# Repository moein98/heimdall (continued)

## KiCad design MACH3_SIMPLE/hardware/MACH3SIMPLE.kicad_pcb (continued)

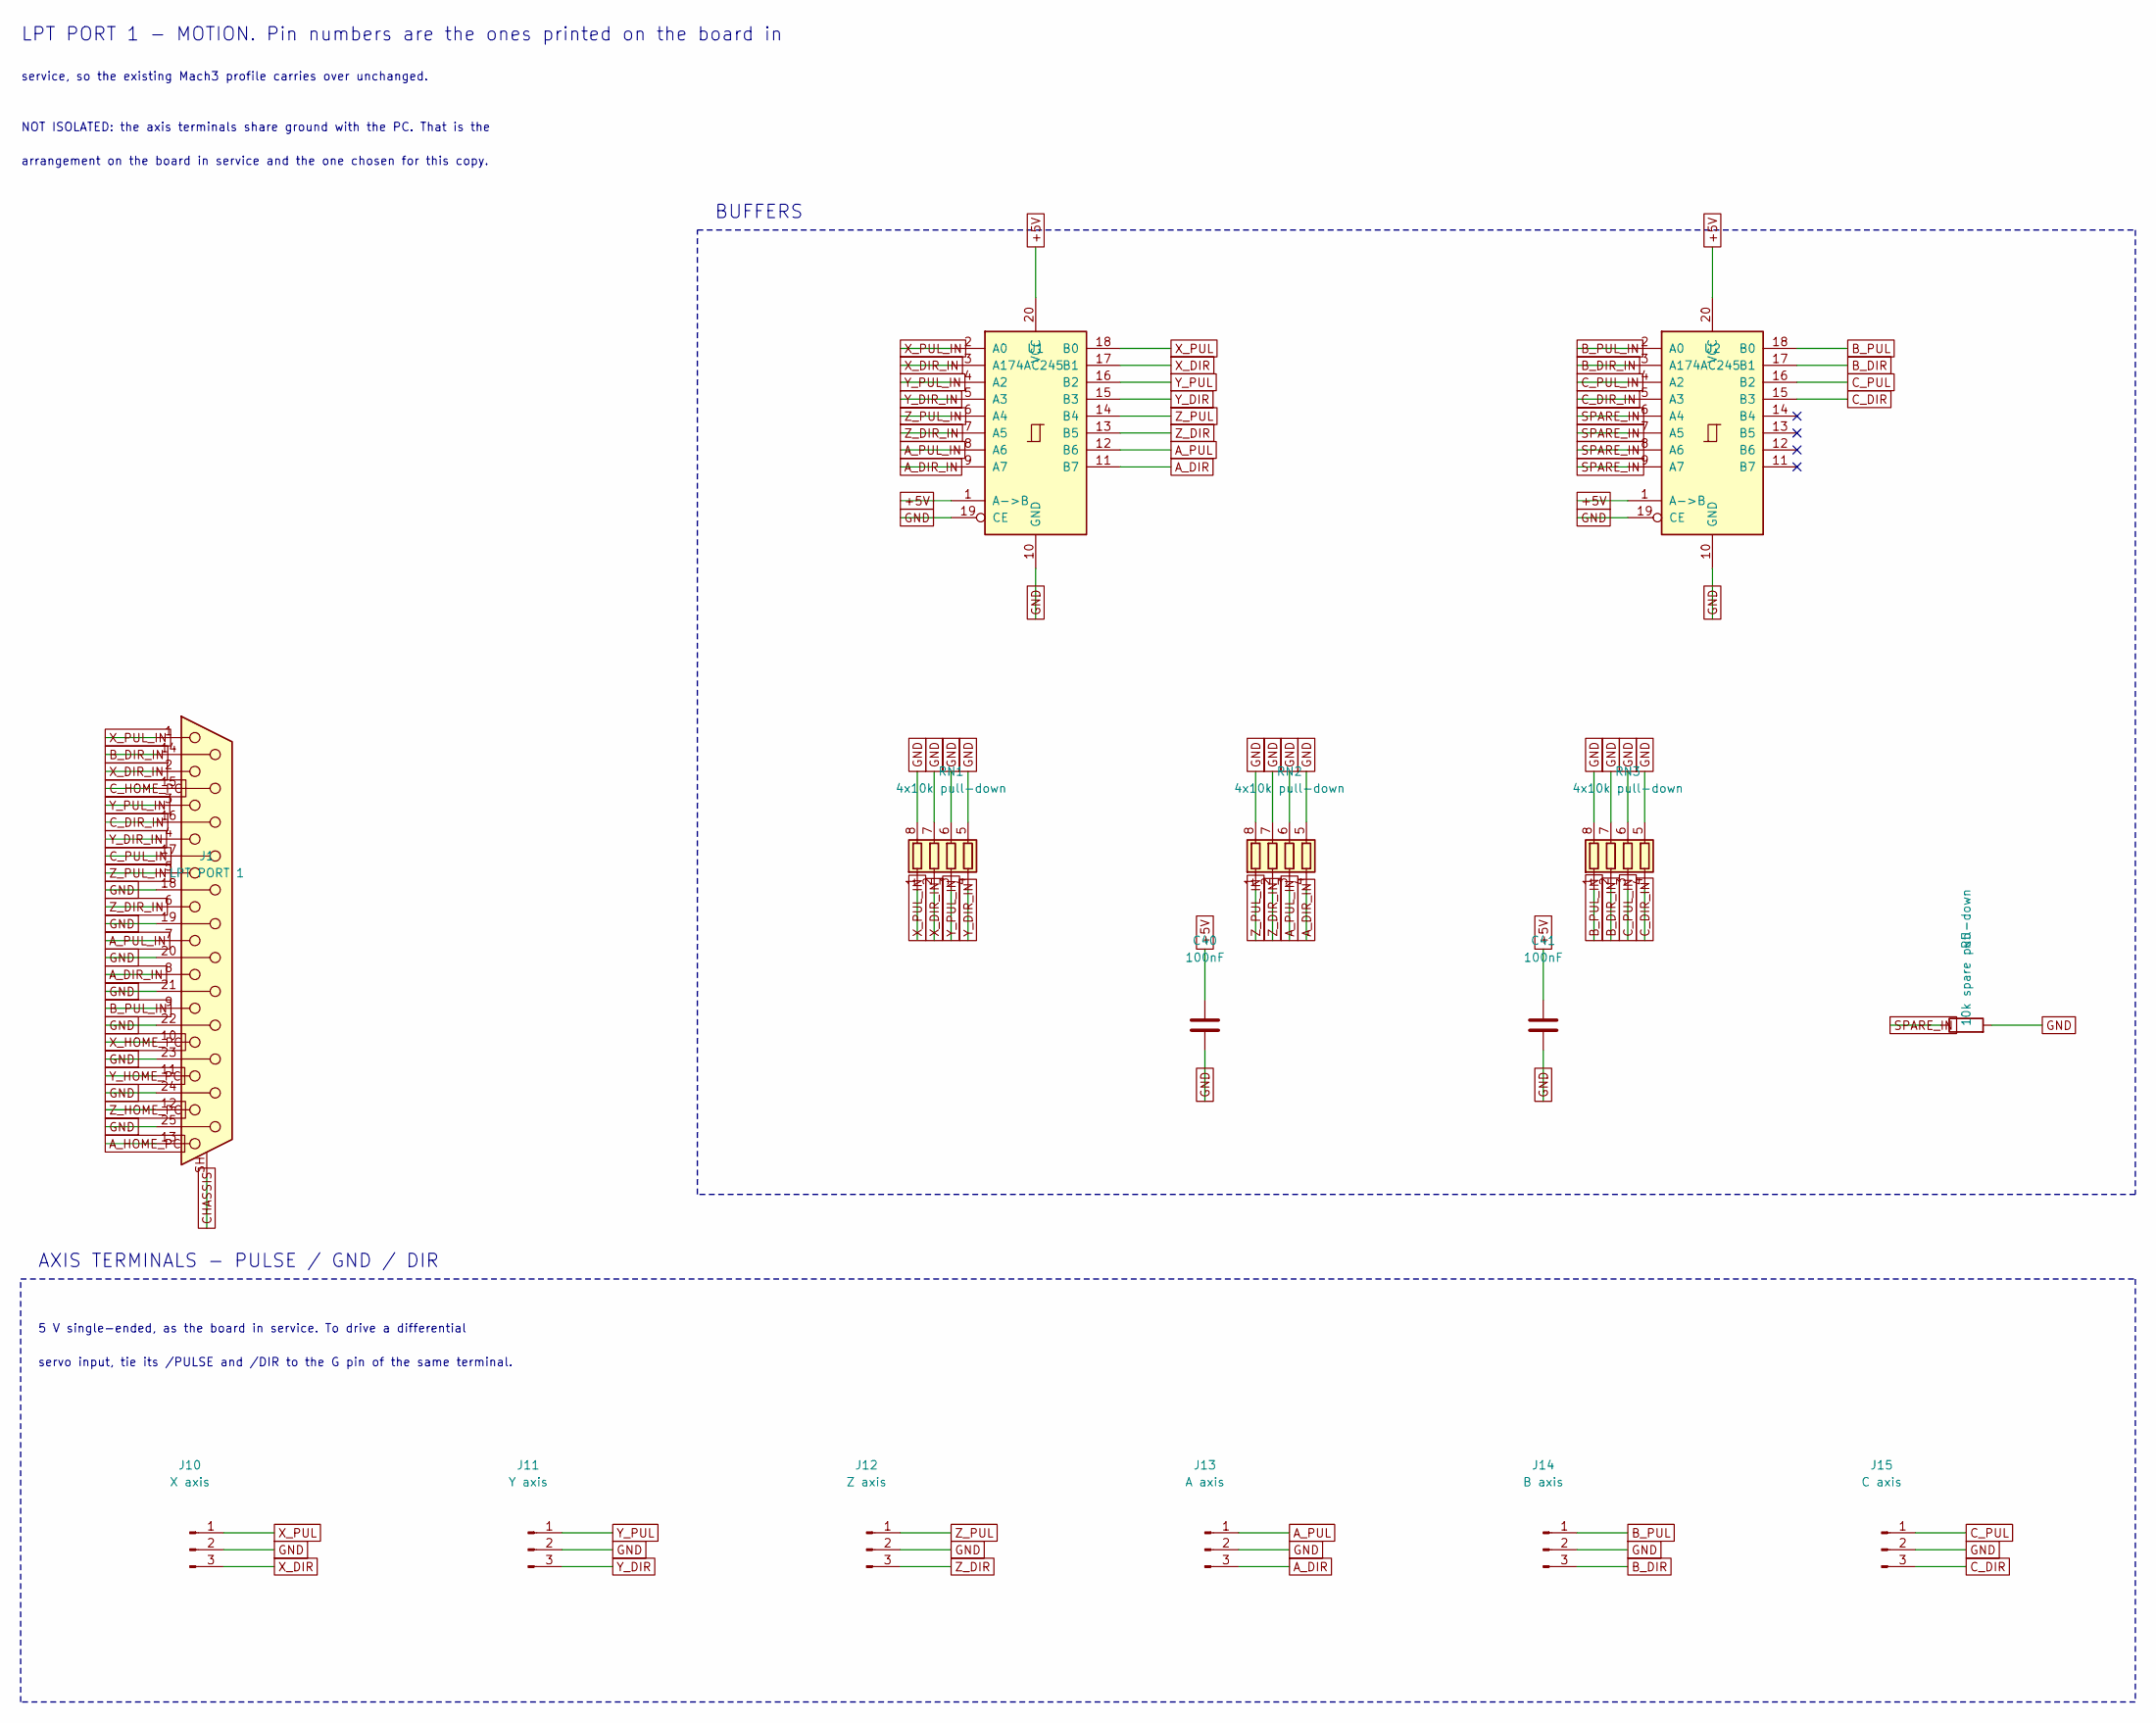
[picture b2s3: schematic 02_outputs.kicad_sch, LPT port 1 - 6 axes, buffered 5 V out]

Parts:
C40, C41: 100nF; C_0603_1608Metric
J1: LPT PORT 1; DSUB-25_Socket_Horizontal_P2.77x2.84mm_EdgePinOffset7.70mm_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
J10: X axis; TerminalBlock_Phoenix_MKDS-1,5-3_1x03_P5.00mm_Horizontal
J11: Y axis; TerminalBlock_Phoenix_MKDS-1,5-3_1x03_P5.00mm_Horizontal
J12: Z axis; TerminalBlock_Phoenix_MKDS-1,5-3_1x03_P5.00mm_Horizontal
J13: A axis; TerminalBlock_Phoenix_MKDS-1,5-3_1x03_P5.00mm_Horizontal
J14: B axis; TerminalBlock_Phoenix_MKDS-1,5-3_1x03_P5.00mm_Horizontal
J15: C axis; TerminalBlock_Phoenix_MKDS-1,5-3_1x03_P5.00mm_Horizontal
R5: 10k spare pull-down; R_0603_1608Metric
RN1, RN2, RN3: 4x10k pull-down; R_Array_Convex_4x0603
U1, U2: 74AC245; SOIC-20W_7.5x12.8mm_P1.27mm

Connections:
+5V: C40.1, C41.1, U1.1 (A->B), U1.20 (VCC), U2.1 (A->B), U2.20 (VCC); also elsewhere on the board
A_DIR: J13.3, U1.11 (B7)
A_DIR_IN: J1.8, RN2.4 (R4.1), U1.9 (A7)
A_HOME_PC: J1.13; also elsewhere on the board
A_PUL: J13.1, U1.12 (B6)
A_PUL_IN: J1.7, RN2.3 (R3.1), U1.8 (A6)
B_DIR: J14.3, U2.17 (B1)
B_DIR_IN: J1.14, RN3.2 (R2.1), U2.3 (A1)
B_PUL: J14.1, U2.18 (B0)
B_PUL_IN: J1.9, RN3.1 (R1.1), U2.2 (A0)
CHASSIS: J1.SH (PAD); also elsewhere on the board
C_DIR: J15.3, U2.15 (B3)
C_DIR_IN: J1.16, RN3.4 (R4.1), U2.5 (A3)
C_HOME_PC: J1.15; also elsewhere on the board
C_PUL: J15.1, U2.16 (B2)
C_PUL_IN: J1.17, RN3.3 (R3.1), U2.4 (A2)
GND: C40.2, C41.2, J1.18, J1.19, J1.20, J1.21, J1.22, J1.23, J1.24, J1.25, J10.2, J11.2, J12.2, J13.2, J14.2, J15.2, R5.2, RN1.5 (R4.2), RN1.6 (R3.2), RN1.7 (R2.2), RN1.8 (R1.2), RN2.5 (R4.2), RN2.6 (R3.2), RN2.7 (R2.2), RN2.8 (R1.2), RN3.5 (R4.2), RN3.6 (R3.2), RN3.7 (R2.2), RN3.8 (R1.2), U1.10 (GND), U1.19 (CE), U2.10 (GND), U2.19 (CE); also elsewhere on the board
SPARE_IN: R5.1, U2.6 (A4), U2.7 (A5), U2.8 (A6), U2.9 (A7)
X_DIR: J10.3, U1.17 (B1)
X_DIR_IN: J1.2, RN1.2 (R2.1), U1.3 (A1)
X_HOME_PC: J1.10; also elsewhere on the board
X_PUL: J10.1, U1.18 (B0)
X_PUL_IN: J1.1, RN1.1 (R1.1), U1.2 (A0)
Y_DIR: J11.3, U1.15 (B3)
Y_DIR_IN: J1.4, RN1.4 (R4.1), U1.5 (A3)
Y_HOME_PC: J1.11; also elsewhere on the board
Y_PUL: J11.1, U1.16 (B2)
Y_PUL_IN: J1.3, RN1.3 (R3.1), U1.4 (A2)
Z_DIR: J12.3, U1.13 (B5)
Z_DIR_IN: J1.6, RN2.2 (R2.1), U1.7 (A5)
Z_HOME_PC: J1.12; also elsewhere on the board
Z_PUL: J12.1, U1.14 (B4)
Z_PUL_IN: J1.5, RN2.1 (R1.1), U1.6 (A4)

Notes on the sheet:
LPT PORT 1 - MOTION. Pin numbers are the ones printed on the board in
service, so the existing Mach3 profile carries over unchanged.
NOT ISOLATED: the axis terminals share ground with the PC. That is the
arrangement on the board in service and the one chosen for this copy.
BUFFERS
AXIS TERMINALS - PULSE / GND / DIR
5 V single-ended, as the board in service. To drive a differential
servo input, tie its /PULSE and /DIR to the G pin of the same terminal.

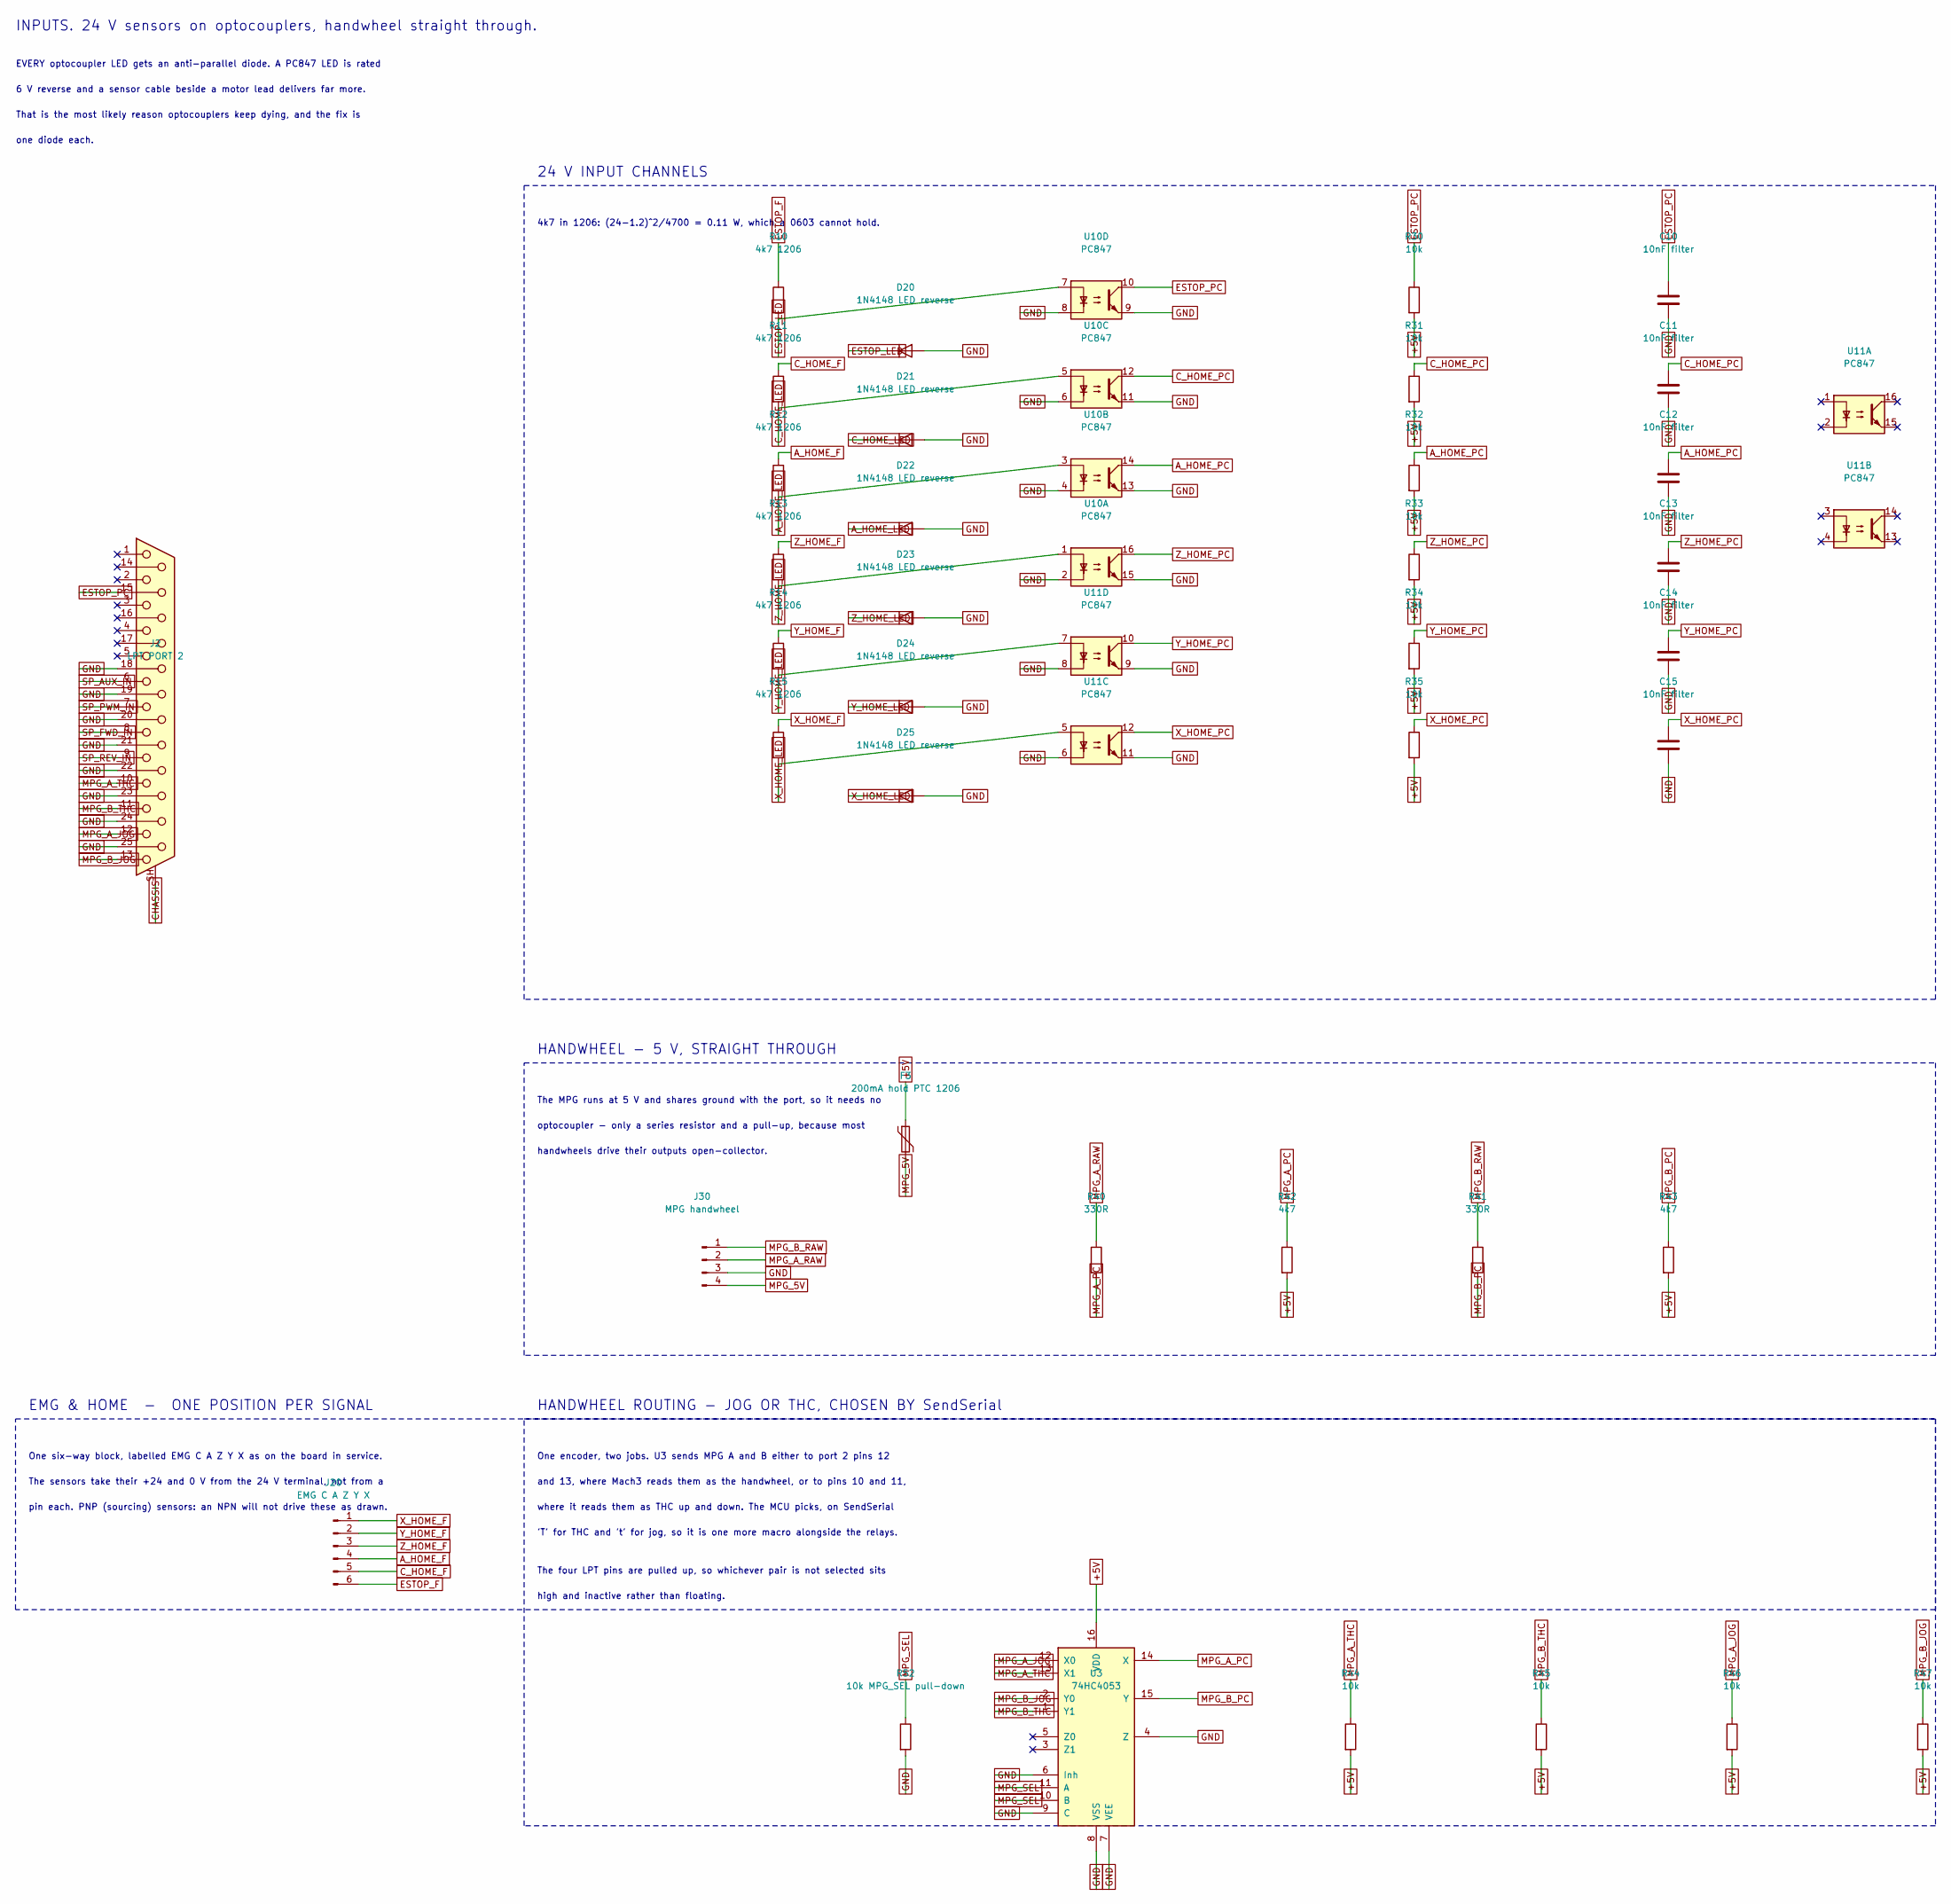
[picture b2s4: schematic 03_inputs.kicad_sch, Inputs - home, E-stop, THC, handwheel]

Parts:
C10, C11, C12, C13, C14, C15: 10nF filter; C_0603_1608Metric
D20, D21, D22, D23, D24, D25: 1N4148 LED reverse; D_SOD-123
F3: 200mA hold PTC 1206; Fuse_1206_3216Metric
J2: LPT PORT 2; DSUB-25_Socket_Horizontal_P2.77x2.84mm_EdgePinOffset7.70mm_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
J20: EMG C A Z Y X; TerminalBlock_Phoenix_MKDS-1,5-6_1x06_P5.00mm_Horizontal
J30: MPG handwheel; TerminalBlock_Phoenix_MKDS-1,5-4_1x04_P5.00mm_Horizontal
R10, R11, R12, R13, R14, R15: 4k7 1206; R_1206_3216Metric
R30, R31, R32, R33, R34, R35, R44, R45, R46, R47: 10k; R_0603_1608Metric
R40, R41: 330R; R_0603_1608Metric
R42, R43: 4k7; R_0603_1608Metric
R52: 10k MPG_SEL pull-down; R_0603_1608Metric
U3: 74HC4053; SOIC-16_3.9x9.9mm_P1.27mm
U10, U11: PC847; SMDIP-16_W9.53mm

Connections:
+5V: F3.1, R30.2, R31.2, R32.2, R33.2, R34.2, R35.2, R42.2, R43.2, R44.2, R45.2, R46.2, R47.2, U3.16 (VDD); also elsewhere on the board
A_HOME_F: J20.4, R12.1
A_HOME_LED: D22.1 (K), R12.2, U10.3
A_HOME_PC: C12.1, R32.1, U10.14; also elsewhere on the board
CHASSIS: J2.SH (PAD); also elsewhere on the board
C_HOME_F: J20.5, R11.1
C_HOME_LED: D21.1 (K), R11.2, U10.5
C_HOME_PC: C11.1, R31.1, U10.12; also elsewhere on the board
ESTOP_F: J20.6, R10.1
ESTOP_LED: D20.1 (K), R10.2, U10.7
ESTOP_PC: C10.1, J2.15, R30.1, U10.10
GND: C10.2, C11.2, C12.2, C13.2, C14.2, C15.2, D20.2 (A), D21.2 (A), D22.2 (A), D23.2 (A), D24.2 (A), D25.2 (A), J2.18, J2.19, J2.20, J2.21, J2.22, J2.23, J2.24, J2.25, J30.3, R52.2, U3.4 (Z), U3.6 (Inh), U3.7 (VEE), U3.8 (VSS), U3.9 (C), U10.2, U10.4, U10.6, U10.8, U10.9, U10.11, U10.13, U10.15, U11.6, U11.8, U11.9, U11.11; also elsewhere on the board
MPG_5V: F3.2, J30.4
MPG_A_JOG: J2.12, R46.1, U3.12 (X0)
MPG_A_PC: R40.2, R42.1, U3.14 (X)
MPG_A_RAW: J30.2, R40.1
MPG_A_THC: J2.10, R44.1, U3.13 (X1)
MPG_B_JOG: J2.13, R47.1, U3.2 (Y0)
MPG_B_PC: R41.2, R43.1, U3.15 (Y)
MPG_B_RAW: J30.1, R41.1
MPG_B_THC: J2.11, R45.1, U3.1 (Y1)
MPG_SEL: R52.1, U3.10 (B), U3.11 (A); also elsewhere on the board
SP_AUX_IN: J2.6; also elsewhere on the board
SP_FWD_IN: J2.8; also elsewhere on the board
SP_PWM_IN: J2.7; also elsewhere on the board
SP_REV_IN: J2.9; also elsewhere on the board
X_HOME_F: J20.1, R15.1
X_HOME_LED: D25.1 (K), R15.2, U11.5
X_HOME_PC: C15.1, R35.1, U11.12; also elsewhere on the board
Y_HOME_F: J20.2, R14.1
Y_HOME_LED: D24.1 (K), R14.2, U11.7
Y_HOME_PC: C14.1, R34.1, U11.10; also elsewhere on the board
Z_HOME_F: J20.3, R13.1
Z_HOME_LED: D23.1 (K), R13.2, U10.1
Z_HOME_PC: C13.1, R33.1, U10.16; also elsewhere on the board

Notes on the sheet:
INPUTS. 24 V sensors on optocouplers, handwheel straight through.
EVERY optocoupler LED gets an anti-parallel diode. A PC847 LED is rated
6 V reverse and a sensor cable beside a motor lead delivers far more.
That is the most likely reason optocouplers keep dying, and the fix is
one diode each.
24 V INPUT CHANNELS
4k7 in 1206: (24-1.2)^2/4700 = 0.11 W, which a 0603 cannot hold.
HANDWHEEL - 5 V, STRAIGHT THROUGH
The MPG runs at 5 V and shares ground with the port, so it needs no
optocoupler - only a series resistor and a pull-up, because most
handwheels drive their outputs open-collector.
HANDWHEEL ROUTING - JOG OR THC, CHOSEN BY SendSerial
One encoder, two jobs. U3 sends MPG A and B either to port 2 pins 12
and 13, where Mach3 reads them as the handwheel, or to pins 10 and 11,
where it reads them as THC up and down. The MCU picks, on SendSerial
'T' for THC and 't' for jog, so it is one more macro alongside the relays.
The four LPT pins are pulled up, so whichever pair is not selected sits
high and inactive rather than floating.
EMG & HOME - ONE POSITION PER SIGNAL
One six-way block, labelled EMG C A Z Y X as on the board in service.
The sensors take their +24 and 0 V from the 24 V terminal, not from a
pin each. PNP (sourcing) sensors: an NPN will not drive these as drawn.

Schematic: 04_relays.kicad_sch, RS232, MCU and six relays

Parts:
C20, C21, C22, C23, C30, C31, C32, C42: 100nF; C_0603_1608Metric
C33, C34: 22pF; C_0603_1608Metric
C35: 10nF; C_0603_1608Metric
D30: SERIAL; LED_0603_1608Metric
D40, D41, D42, D43, D44, D45: 1N4148 flyback; D_SOD-123
D50: KA; LED_0603_1608Metric
D51: KB; LED_0603_1608Metric
D52: KC; LED_0603_1608Metric
D53: KD; LED_0603_1608Metric
D54: KE; LED_0603_1608Metric
D55: KF; LED_0603_1608Metric
J40: Relay A; TerminalBlock_Phoenix_MKDS-1,5-3_1x03_P5.00mm_Horizontal
J41: Relay B; TerminalBlock_Phoenix_MKDS-1,5-3_1x03_P5.00mm_Horizontal
J42: Relay C; TerminalBlock_Phoenix_MKDS-1,5-3_1x03_P5.00mm_Horizontal
J43: Relay D; TerminalBlock_Phoenix_MKDS-1,5-3_1x03_P5.00mm_Horizontal
J44: Relay E; TerminalBlock_Phoenix_MKDS-1,5-3_1x03_P5.00mm_Horizontal
J45: Relay F; TerminalBlock_Phoenix_MKDS-1,5-3_1x03_P5.00mm_Horizontal
J50: RS232 RX TX GND; TerminalBlock_Phoenix_MKDS-1,5-3_1x03_P5.00mm_Horizontal
J60: ICSP; IDC-Header_2x05_P2.54mm_Vertical
K1, K2, K3, K4, K5, K6: JQC-3FF-024-1Z; Relay_SPDT_Hongfa_JQC-3FF_0XX-1Z
Q1, Q2, Q3, Q4, Q5, Q6: 2N7002; SOT-23
R50, R70, R71, R72, R73, R74, R75, R80, R81, R82, R83, R84, R85: 10k; R_0603_1608Metric
R51, R60, R61, R62, R63, R64, R65: 1k; R_0603_1608Metric
U20: MAX3232; SOIC-16_3.9x9.9mm_P1.27mm
U21: ATmega328P-AU; TQFP-32_7x7mm_P0.8mm
Y1: 16MHz; Crystal_SMD_3225-4Pin_3.2x2.5mm

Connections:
+5V: C22.2, C30.1, C31.1, C32.1, C42.1, J60.2 (VCC), R50.2, U20.16 (VCC), U21.4 (VCC), U21.6 (VCC), U21.18 (AVCC); also elsewhere on the board
C1N: C20.2, U20.3 (C1-)
C1P: C20.1, U20.1 (C1+)
C2N: C21.2, U20.5 (C2-)
C2P: C21.1, U20.4 (C2+)
GND: C23.2, C30.2, C31.2, C32.2, C33.2, C34.2, C35.2, C42.2, D30.1 (K), J50.3, J60.4 (GND), J60.6 (GND), J60.8 (GND), J60.10 (GND), Q1.2 (S), Q2.2 (S), Q3.2 (S), Q4.2 (S), Q5.2 (S), Q6.2 (S), R70.2, R71.2, R72.2, R73.2, R74.2, R75.2, U20.8 (R2IN), U20.10 (T2IN), U20.15 (GND), U21.3 (GND), U21.5 (GND), U21.19 (ADC6), U21.21 (GND), U21.22 (ADC7), Y1.2 (G), Y1.4 (G); also elsewhere on the board
ICSP_MISO: J60.9 (MISO), U21.16 (PB4)
ICSP_MOSI: J60.1 (MOSI), U21.15 (PB3)
ICSP_SCK: J60.7 (SCK), U21.17 (PB5)
KA_COM: J40.2, K1.11
KA_NC: J40.3, K1.12
KA_NO: J40.1, K1.14
KB_COM: J41.2, K2.11
KB_NC: J41.3, K2.12
KB_NO: J41.1, K2.14
KC_COM: J42.2, K3.11
KC_NC: J42.3, K3.12
KC_NO: J42.1, K3.14
KD_COM: J43.2, K4.11
KD_NC: J43.3, K4.12
KD_NO: J43.1, K4.14
KE_COM: J44.2, K5.11
KE_NC: J44.3, K5.12
KE_NO: J44.1, K5.14
KF_COM: J45.2, K6.11
KF_NC: J45.3, K6.12
KF_NO: J45.1, K6.14
MCU_LED: R51.1, U21.14 (PB2)
MCU_RESET: C35.1, J60.5 (~RST), R50.1, U21.29 (~RESET/PC6)
MCU_RX: U20.12 (R1OUT), U21.30 (PD0)
MCU_TX: U20.11 (T1IN), U21.31 (PD1)
MPG_SEL: U21.13 (PB1); also elsewhere on the board
unnamed: D30.2 (A), R51.2
unnamed: D50.2 (A), R80.2
unnamed: D51.2 (A), R81.2
unnamed: D52.2 (A), R82.2
unnamed: D53.2 (A), R83.2
unnamed: D54.2 (A), R84.2
unnamed: D55.2 (A), R85.2
unnamed: Q1.1 (G), R60.2
unnamed: Q2.1 (G), R61.2
unnamed: Q3.1 (G), R62.2
unnamed: Q4.1 (G), R63.2
unnamed: Q5.1 (G), R64.2
unnamed: Q6.1 (G), R65.2
RELC_A: D40.2 (A), D50.1 (K), K1.A2, Q1.3 (D)
RELC_B: D41.2 (A), D51.1 (K), K2.A2, Q2.3 (D)
RELC_C: D42.2 (A), D52.1 (K), K3.A2, Q3.3 (D)
RELC_D: D43.2 (A), D53.1 (K), K4.A2, Q4.3 (D)
RELC_E: D44.2 (A), D54.1 (K), K5.A2, Q5.3 (D)
RELC_F: D45.2 (A), D55.1 (K), K6.A2, Q6.3 (D)
REL_A: R60.1, R70.1, U21.1 (PD3)
REL_B: R61.1, R71.1, U21.2 (PD4)
REL_C: R62.1, R72.1, U21.9 (PD5)
REL_D: R63.1, R73.1, U21.10 (PD6)
REL_E: R64.1, R74.1, U21.11 (PD7)
REL_F: R65.1, R75.1, U21.12 (PB0)
RS232_RX: J50.1, U20.13 (R1IN)
RS232_TX: J50.2, U20.14 (T1OUT)
V24: D40.1 (K), D41.1 (K), D42.1 (K), D43.1 (K), D44.1 (K), D45.1 (K), K1.A1, K2.A1, K3.A1, K4.A1, K5.A1, K6.A1, R80.1, R81.1, R82.1, R83.1, R84.1, R85.1; also elsewhere on the board
VSN: C23.1, U20.6 (VS-)
VSP: C22.1, U20.2 (VS+)
XTAL1: C33.1, U21.7 (XTAL1/PB6), Y1.3
XTAL2: C34.1, U21.8 (XTAL2/PB7), Y1.1

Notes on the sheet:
RS232 RELAY BANK. SendSerial("A").."F" on, "a".."f" off - the same
protocol as the board in service, so existing macros keep working.
RS232 AND MCU
The ATmega arrives blank: program it through J60 with a USBasp
(firmware/build.sh flash), which also sets the fuses for the 16 MHz
crystal Y1: low FF, high D9, extended FD. The factory fuses select the
internal RC, which is trimmed only to 10 percent. Serial is 9600 8N1.
SIX RELAYS - 24 V COILS ONLY
The contacts switch 24 V Finder coils. Nothing on this board touches
mains. A Finder coil is 20-60 mA, so a 10 A contact is heavily derated.

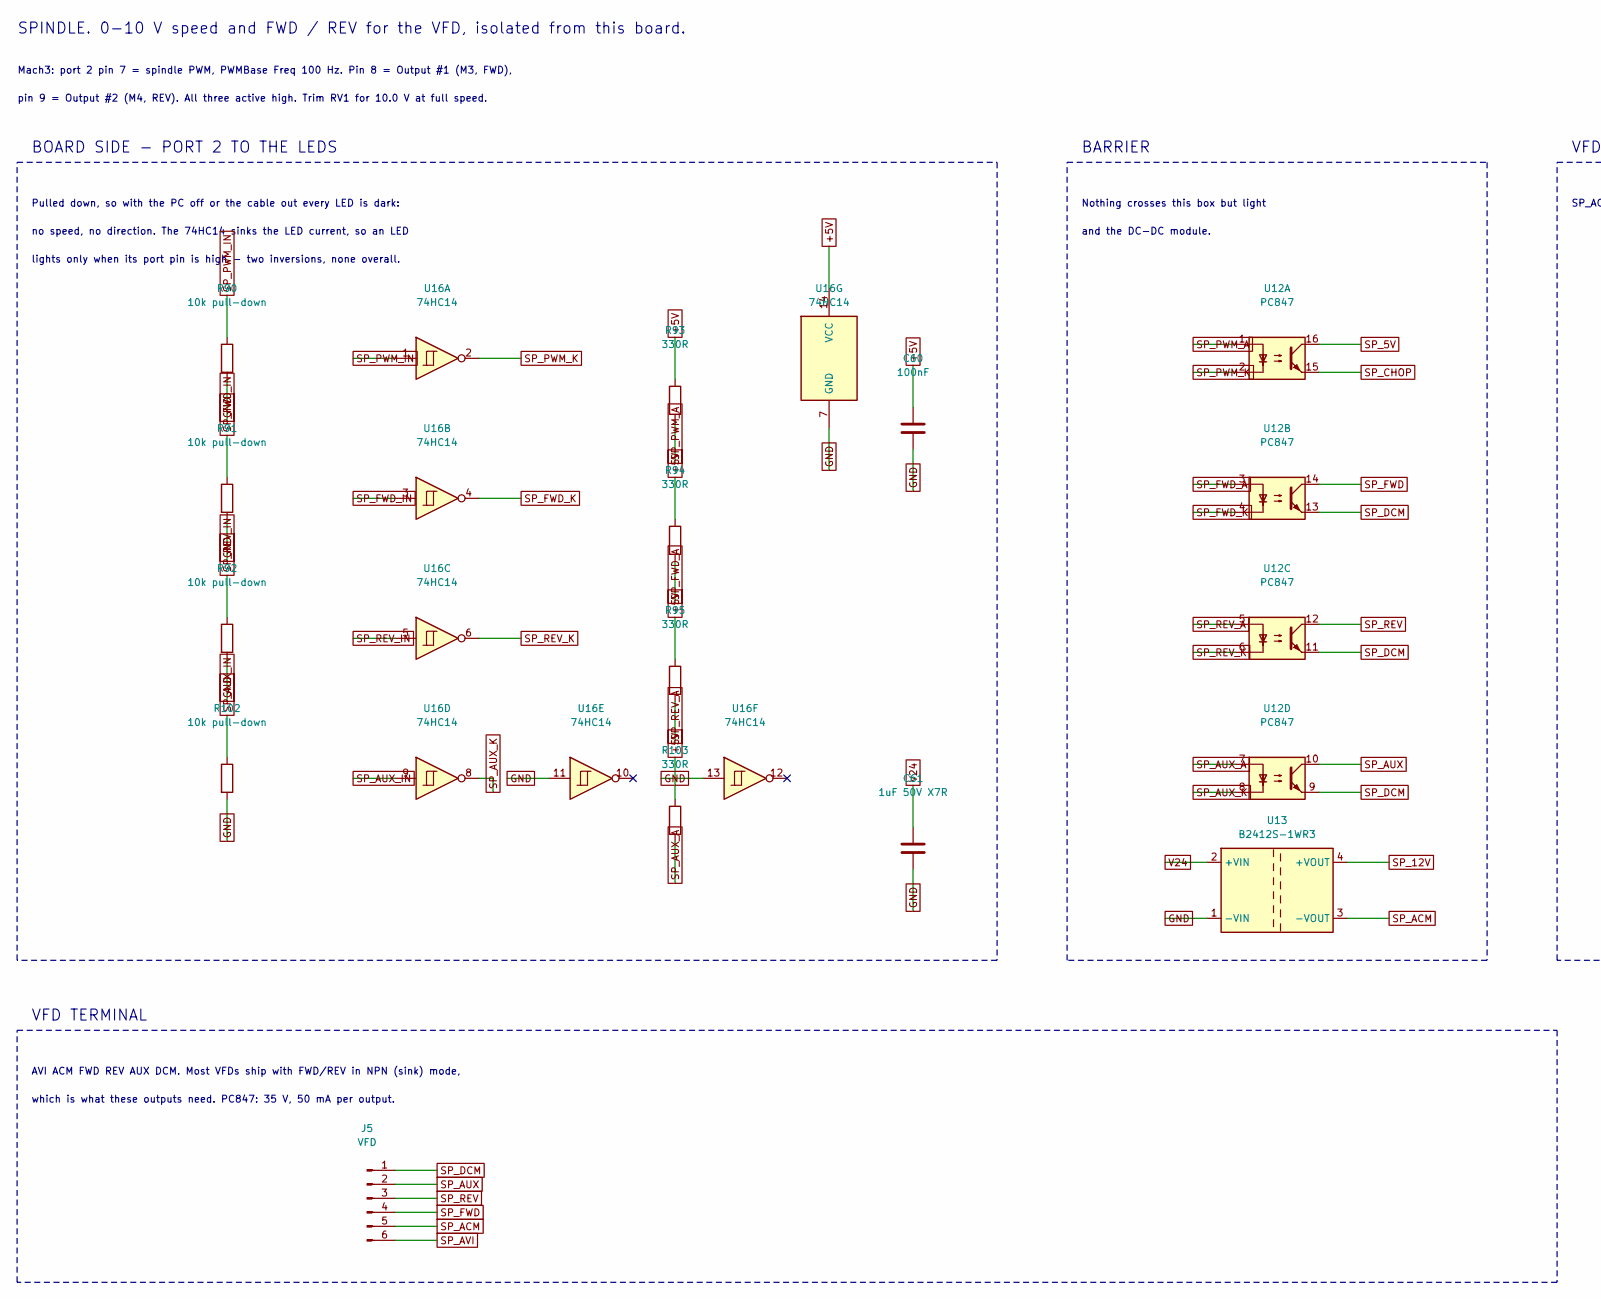
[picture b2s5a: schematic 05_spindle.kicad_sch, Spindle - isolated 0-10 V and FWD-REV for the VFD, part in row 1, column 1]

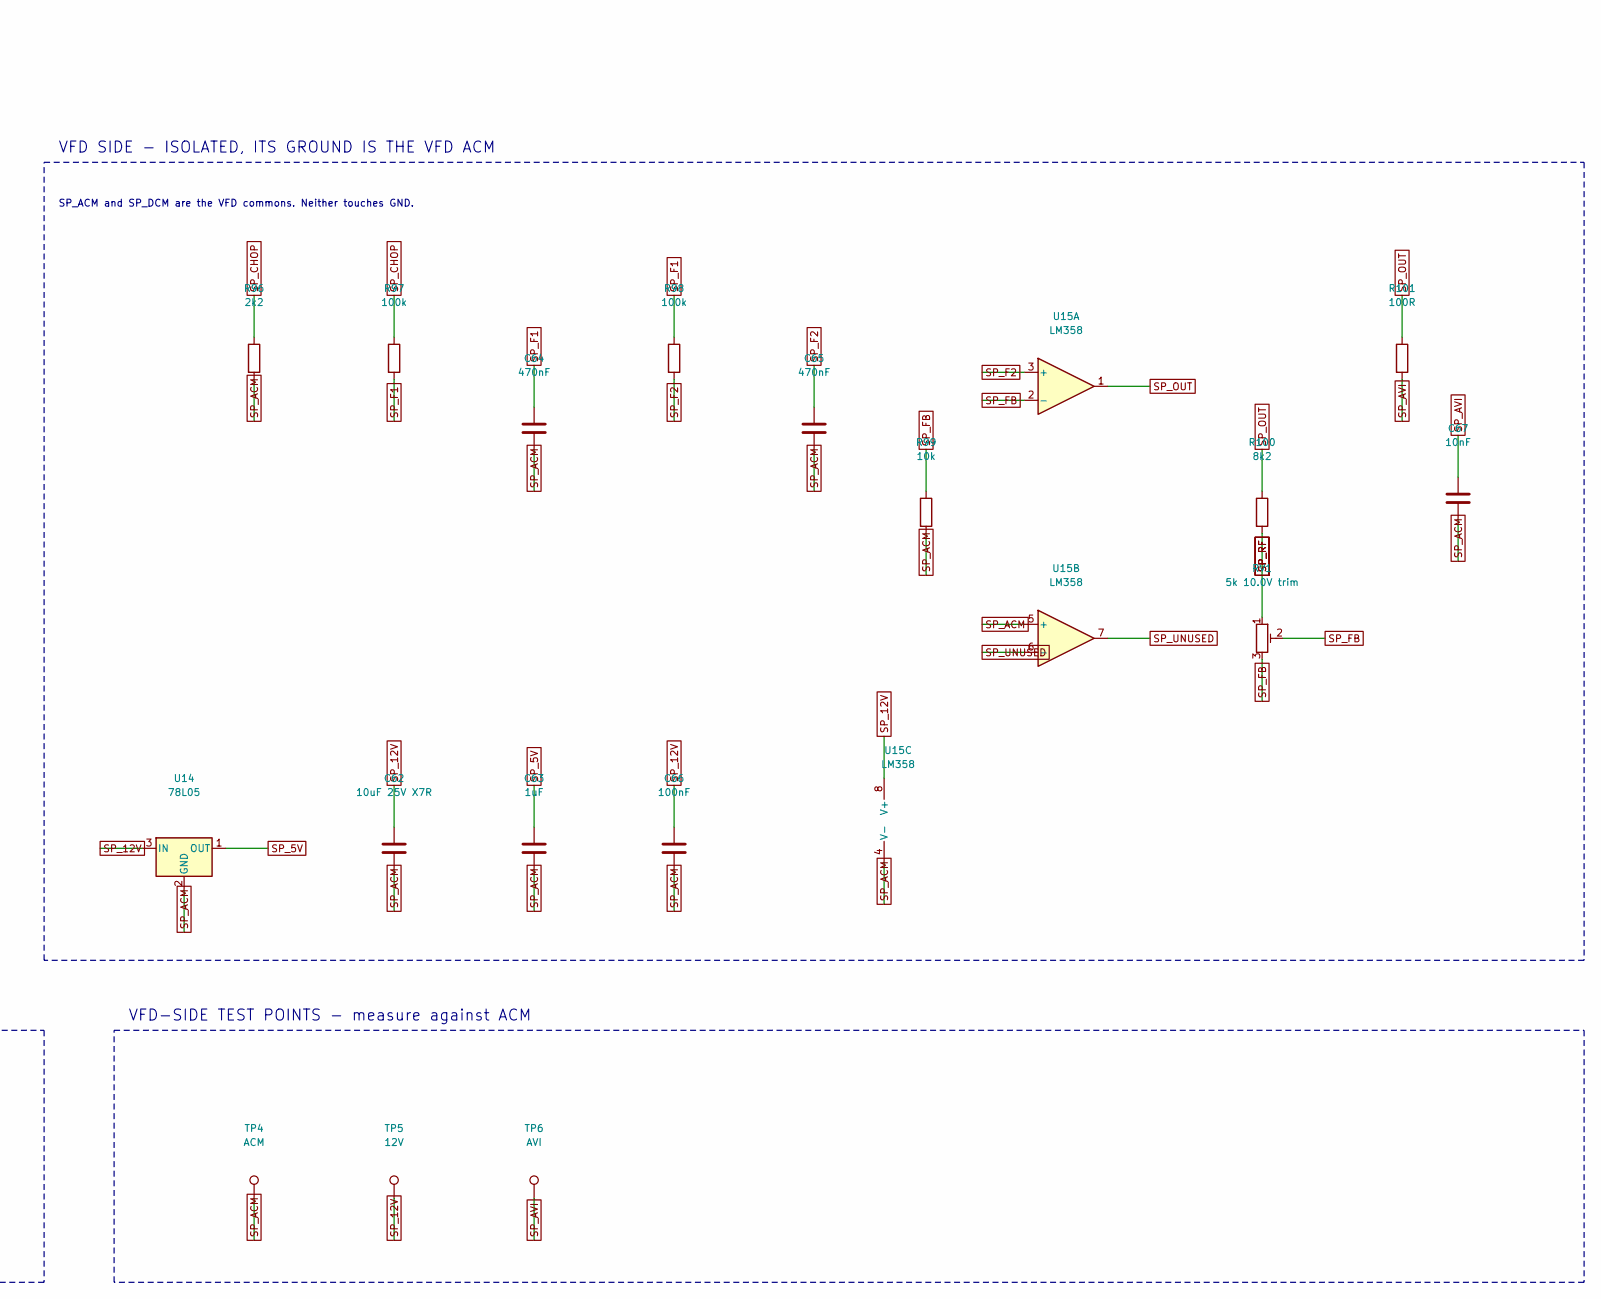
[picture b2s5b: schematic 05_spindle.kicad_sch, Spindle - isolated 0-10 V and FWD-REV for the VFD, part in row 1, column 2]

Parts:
C60, C66: 100nF; C_0603_1608Metric
C61: 1uF 50V X7R; C_1206_3216Metric
C62: 10uF 25V X7R; C_1206_3216Metric
C63: 1uF; C_0603_1608Metric
C64, C65: 470nF; C_0603_1608Metric
C67: 10nF; C_0603_1608Metric
J5: VFD; TerminalBlock_Phoenix_MKDS-1,5-6_1x06_P5.00mm_Horizontal
R90, R91, R92, R102: 10k pull-down; R_0603_1608Metric
R93, R94, R95, R103: 330R; R_0603_1608Metric
R96: 2k2; R_0603_1608Metric
R97, R98: 100k; R_0603_1608Metric
R99: 10k; R_0603_1608Metric
R100: 8k2; R_0603_1608Metric
R101: 100R; R_0603_1608Metric
RV1: 5k 10.0V trim; Potentiometer_Bourns_3296W_Vertical
TP4: ACM; TestPoint_THTPad_D2.0mm_Drill1.0mm
TP5: 12V; TestPoint_THTPad_D2.0mm_Drill1.0mm
TP6: AVI; TestPoint_THTPad_D2.0mm_Drill1.0mm
U12: PC847; SMDIP-16_W9.53mm
U13: B2412S-1WR3; Converter_DCDC_Murata_CRE1xxxxxxSC_THT
U14: 78L05; SOT-89-3
U15: LM358; SOIC-8_3.9x4.9mm_P1.27mm
U16: 74HC14; SOIC-14_3.9x8.7mm_P1.27mm

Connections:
+5V: C60.1, R93.1, R94.1, R95.1, R103.1, U16.14 (VCC); also elsewhere on the board
GND: C60.2, C61.2, R90.2, R91.2, R92.2, R102.2, U13.1 (-VIN), U16.7 (GND), U16.11, U16.13; also elsewhere on the board
SP_5V: C63.1, U12.16, U14.1 (OUT)
SP_12V: C62.1, C66.1, TP5.1, U13.4 (+VOUT), U14.3 (IN), U15.8 (V+)
SP_ACM: C62.2, C63.2, C64.2, C65.2, C66.2, C67.2, J5.5, R96.2, R99.2, TP4.1, U13.3 (-VOUT), U14.2 (GND), U15.4 (V-), U15.5 (+)
SP_AUX: J5.2, U12.10
SP_AUX_A: R103.2, U12.7
SP_AUX_IN: R102.1, U16.9; also elsewhere on the board
SP_AUX_K: U12.8, U16.8
SP_AVI: C67.1, J5.6, R101.2, TP6.1
SP_CHOP: R96.1, R97.1, U12.15
SP_DCM: J5.1, U12.9, U12.11, U12.13
SP_F1: C64.1, R97.2, R98.1
SP_F2: C65.1, R98.2, U15.3 (+)
SP_FB: R99.1, RV1.2, RV1.3, U15.2 (-)
SP_FWD: J5.4, U12.14
SP_FWD_A: R94.2, U12.3
SP_FWD_IN: R91.1, U16.3; also elsewhere on the board
SP_FWD_K: U12.4, U16.4
SP_OUT: R100.1, R101.1, U15.1
SP_PWM_A: R93.2, U12.1
SP_PWM_IN: R90.1, U16.1; also elsewhere on the board
SP_PWM_K: U12.2, U16.2
SP_REV: J5.3, U12.12
SP_REV_A: R95.2, U12.5
SP_REV_IN: R92.1, U16.5; also elsewhere on the board
SP_REV_K: U12.6, U16.6
SP_RF: R100.2, RV1.1
SP_UNUSED: U15.6 (-), U15.7
V24: C61.1, U13.2 (+VIN); also elsewhere on the board

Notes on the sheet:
SPINDLE. 0-10 V speed and FWD / REV for the VFD, isolated from this board.
Mach3: port 2 pin 7 = spindle PWM, PWMBase Freq 100 Hz. Pin 8 = Output #1 (M3, FWD),
pin 9 = Output #2 (M4, REV). All three active high. Trim RV1 for 10.0 V at full speed.
BOARD SIDE - PORT 2 TO THE LEDS
Pulled down, so with the PC off or the cable out every LED is dark:
no speed, no direction. The 74HC14 sinks the LED current, so an LED
lights only when its port pin is high - two inversions, none overall.
BARRIER
Nothing crosses this box but light
and the DC-DC module.
VFD SIDE - ISOLATED, ITS GROUND IS THE VFD ACM
SP_ACM and SP_DCM are the VFD commons. Neither touches GND.
VFD-SIDE TEST POINTS - measure against ACM
VFD TERMINAL
AVI ACM FWD REV AUX DCM. Most VFDs ship with FWD/REV in NPN (sink) mode,
which is what these outputs need. PC847: 35 V, 50 mA per output.
